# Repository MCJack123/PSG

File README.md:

# JackMacWindows's Programmable Sound Generator
This repo contains the source code for my programmable sound generation board. [Read the article for more info.](https://mcjack123.github.io/PSG/)

## Contents
* `PSG-PCB` is a KiCad PCB layout for the complete 16-channel board.
* `PSG.X` contains an MPLAB X project with the wave generator code for the microcontrollers.
* `pico-sound-driver` contains a Raspberry Pi Pico project for managing the MCUs with a USB MIDI interface.
* `sound-midi.cpp` is a CraftOS-PC plugin for connecting to the board using the `sound` plugin interface.
* `programmer.cpp` is a program to quickly flash UF2, HEX, or BIN (concatenated HEX + UF2) firmware files to the PIC chips and the Pico. The current production firmware is available in `firmware.bin`.
* [`instrument-designer.html`](https://mcjack123.github.io/PSG/instrument-designer.html) is a small HTML+JS app to quickly design and upload instrument patches to the board.

## Documentation

### Mono/Poly Mode
The board has two different modes available. These modes are controlled by the standard CCs 126 and 127.

In mono mode, each channel can play one frequency and has its own global program and volume settings. This has a 1:1 correlation with each chip - one MIDI channel controls its corresponding chip number. Instruments are not available in this mode - instead, the program number (from 0-7, looping after) controls the wave type directly, as if the instrument bank was just initialized.

In poly mode, chips are allocated as needed for each note to play. Programs are assigned to each channel, and instruments are available.

### Direct Parameter Control
To support being able to directly control the parameters of each chip, some CCs are added to control the frequency instead of requiring note+pitch bend messages. See below for more information on those. In addition, when in mono mode, the standard volume and program change settings will directly affect the chips.

### Stereo Support
Firmware version 1.2.0 adds support for stereo output on board revisions that support it (v1.2.0 or later). There are three modes available: center (default), split stereo, and full stereo. In split stereo mode, all 16 voices are available, but the first eight will go straight to the left side, and the second eight will go to the right side. This is most effective when in mono note mode. Full stereo reduces the number of available voices to 8, but plays notes with chips on both sides, making them audible on both sides, as well as enabling panning using the CC & envelope.

### Instruments
Instruments allow attaching envelopes to waves for continuous changes to certain parameters. Four envelopes are available for controlling volume, panning, frequency adjustment, and duty cycle (square waves only). Instruments replace basic wave type controls in poly mode, and all 128 programs in MIDI have instruments attached.

Envelopes are based on the XM module format's envelope design. Each envelope has a maximum of 12 points available, each storing 16-bit pairs of X/Y coordinates. The X axis indicates the time of the point, in hundredths of a second. The Y axis stores the MIDI value of the control for everything except frequency. The frequency envelope's Y axis is the number of 16ths of a semitone to offset the note by, with a value of `0x8000` being centered at ±0.

Each envelope also has the ability to loop between certain points. There are three modes: one shot, which plays the envelope straight and ends at the last point, regardless of note off; sustain, which holds the envelope position at the *sustain point* until the note is released; and loop, which jumps the position in the envelope back to the loop start point when it reaches the loop end point. (Sustain mode functions like loop mode as if the start and end point were the same.)

By default, the instrument list is filled with basic instruments with no envelopes. The wave types cycle in the same order as mono mode, but program numbers divisible by 8 hold square waves with increasing default duty levels (for example, program 8 is a 1/16 duty square wave, program 32 is a 1/4 duty square wave, etc.). Program 0 is also set to a 1/2 duty square wave, as a duty of 0 is invalid.

### CC List
This table lists all available CCs.

| CC  | Description |
|-----|-------------|
| 1   | Square wave duty cycle |
| 7   | Volume |
| 10  | Pan (full stereo mode only) |
| 24  | Frequency (MSB) |
| 56  | Frequency (LSB) |
| 86  | Stereo mode: `0x40` -> stereo enable bit, `0x20` -> dual channel bit |
| 123 | All notes off |
| 126 | Mono mode |
| 127 | Poly mode |

### Wave Types
| Code | Wave |
|------|------|
| 0    | None, or square |
| 1    | Sine |
| 2    | Triangle |
| 3    | Saw (ascending) |
| 4    | Saw (descending) |
| 5    | Square |
| 6    | Noise  |
| 7    | Undefined |

### SysEx List
PSG accepts SysEx commands with vendor ID `00 46 71`. Commands are followed by two bytes for the command number in little endian.

| Command | Data | Description |
|---------|------|-------------|
| `00 00` | HEX file | Flash PIC firmware to all attached chips |
| `01 F7` | None | Enter UF2 bootloader mode |
| `02 00` | Patch number, instrument data | Upload instrument data to program slot |

#### Instrument data
Instruments are stored in a 212-byte binary block encoded with Base64. Point coordinates are in little endian.

| Offset | Size | Description |
|--------|------|-------------|
| `0x00` | 2    | X coordinate of first point in volume envelope |
| `0x02` | 2    | Y coordinate of first point in volume envelope |
| `0x04` | 2/2  | X/Y coordinates of second point in volume envelope |
| `0x08` | 40   | ...10 more points |
| `0x30` | 1    | Number of points in volume envelope |
| `0x31` | 1    | Sustain point number in volume envelope (`0xFF` = no sustain) |
| `0x32` | 1    | Loop start point number in volume envelope (`0xFF` = no loop) |
| `0x33` | 1    | Loop end point number in volume envelope (`0xFF` = no loop) |
| `0x34` | 52   | Pan envelope |
| `0x68` | 52   | Frequency envelope |
| `0x9C` | 52   | Duty envelope |
| `0xD0` | 1    | Wave type |
| `0xD1` | 3    | Reserved, set to 0 |

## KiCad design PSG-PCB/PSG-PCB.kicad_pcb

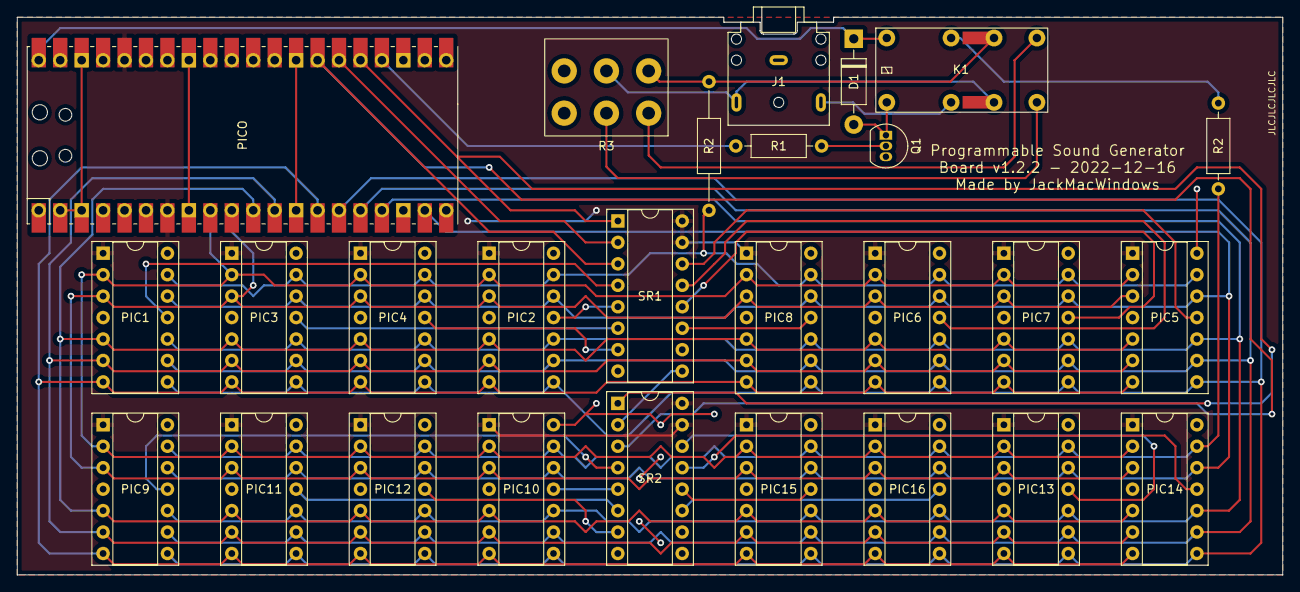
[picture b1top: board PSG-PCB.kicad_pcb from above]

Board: 2 copper layers, 149.8 x 66.0 mm, 9 parts (0 on the bottom side), 12 nets.

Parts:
D1: D_DO-41_SOD81_P10.16mm_Horizontal
J1: Jack_3.5mm_CUI_SJ1-3523N_Horizontal
K1: Relay_DPDT_CIT_J104D
PICO: RPi_Pico_SMD_TH
Q1: TO-92_Inline
R1: 1K; R_Axial_DIN0207_L6.3mm_D2.5mm_P10.16mm_Horizontal
R2: 150K; R_Axial_DIN0207_L6.3mm_D2.5mm_P15.24mm_Horizontal
R2#2: 150K; R_Axial_DIN0207_L6.3mm_D2.5mm_P10.16mm_Horizontal
R3: Potentiometer_Bourns_PDB182-K_Horizontal

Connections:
5V: D1.1, K1.1, PICO.40
Audio_In_Amp: K1.5, R2.2, R3.3
Audio_In_R_Amp: K1.7, R3.6
Audio_In_R_Res: K1.3, R2#2.2
Audio_Out: J1.T, K1.6, R3.2
Audio_Out_R: K1.8, R3.5
Audio_Pin_R: J1.R, K1.4
Ground: J1.S, PICO.1, PICO.2, PICO.3, PICO.4, PICO.5, PICO.6, PICO.8, PICO.13, PICO.18, PICO.23, PICO.28, PICO.33, PICO.38, Q1.3, R3.1, R3.4
Relay_Sink: D1.2, K1.2, Q1.1
Stereo: PICO.24, R1.1
T_Base: Q1.2, R1.2
VDD: PICO.7, PICO.36

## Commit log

2022-05-18 first
2022-05-18 Added meta tags
2022-05-19 Improved audio quality
2022-11-04 Version 1.x Initial Upload
    Documentation and a write-up to come soon.
2022-11-27 Fixed a few things in the Pico code
    (Aftertouch, instrument 0, poly mode not working)
2022-12-09 Added write-up for part 2 (v1.2)
2022-12-09 Fixed final heading
2022-12-09 Added demos, MIDI plugin (oops), tiny fixes
2022-12-17 Added license, removed old files, added version number
2022-12-17 Redesigned board volume control, added version check
2023-01-04 PSG firmware version 1.2.0
    New in this version:
    * Support for stereo cards (untested)
    * Set CC 86 to change stereo mode: 0 = mono, 255 = stereo
    * Added instrument support
    * Automatic envelopes for volume, pan, frequency, duty
    * Based on XM module envelopes, 12 points/envelope
2023-01-04 Added link to instrument designer
2023-01-05 Fixed Firefox support
2023-01-05 Added coordinates to instrument designer
2023-03-27 Added serial number
2023-03-28 Added low-pass filter, protection on bootloader
2023-03-30 Added resonance filter, envelopes
2023-04-14 Added BT support, LCD, knobs, ADSR
